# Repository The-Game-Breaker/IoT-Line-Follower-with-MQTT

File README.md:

# IoT Project
# Hardware
## Gebruikte hardware
### Electronica
| Item                            | Discription                                      | Price    | Qty | Extra costs | Total     |
| ------------------------------- | ------------------------------------------------ | -------- | --- | ----------- | --------- |
| Cytron Maker Line               | Simplifying Line Sensor for BeginnersSKU: 19064  |  11,95 € | 1   |             |  11,95 €  |
| Shipping Sensor                 | Shipping elektor                                 |          | 1   |  7,95 €     |  7,95 €   |
| PCB mainboard                   | PCB robot driver board                           |  0,51 €  | 1   |             |  0,51 €   |
| SHIPPING CHARGE                 | SHIPPING                                         |          | 1   |  12,63 €    |  12,63 €  |
| PAYPAL FEE                      | PAYPAL FEE                                       |          | 1   |  0,41 €     |  0,41 €   |
| DRV8825 driver                  | DSD00010 \_Stepstick DRV8825 drive with heatsink |  5,00 €  | 2   |             |  10,00 €  |
| Inbusstelschroef M4x5           | DBM00194 \_Inbusstelschroef M4x5 (10 stuks)      |  2,30 €  | 1   |             |  2,30 €   |
| Verzend- en administratiekosten | Verzend- en administratiekosten 123-3D.nl        |          | 1   |  5,95 €     |  5,95 €   |
| Lipo Battery                    | Yuki Kryptonium 3S 11.1V 30C 5000mAh LiPo 801323 |  45,99 € | 1   |             |  45,99 €  |
| Step-Down Buck Converter        | DEBO DCDC DOWN 4 (mini 360)                      |  2,02 €  | 1   |             |  2,02 €   |
| Dupont kit                      | Dupont connector kit                             |  5,00 €  | 1   |             |  5,00 €   |
| Fuse holder                     | fuse holder                                      |  0,30 €  | 1   |             |  0,30 €   |
| Fuse                            | fuse 2A                                          |  0,20 €  | 1   |             |  0,20 €   |
| RGB led                         | RGB common cathode                               |  1,03 €  | 2   |             |  2,06 €   |
| 3mm led                         | 3mm led red                                      |  0,05 €  | 2   |             |  0,10 €   |
| Resistors                       | resistors various values                         |  0,02 €  | 8   |             |  0,13 €   |
| HC-SR04                         | HC-SR04 Ultrasonic sensor – afstandsmeter        |  3,00 €  | 1   |             |  3,00 €   |
| capacator                       | capacator                                        |  0,11 €  | 2   |             |  0,22 €   |
| 3D print                        | 3d prints materiaal+manafacturing                |  20,00 € | 1   |             |  20,00 €  |
| Lasercut frame                  | laserkcut frame matriaal+manafacturing           |  20,00 € | 1   |             |  20,00 €  |
| Stepper motor                   | JK42HS34-1334                                    |  13,00 € | 2   |             |  26,00 €  |
| Hardware                        | varous nuts and bolts                            |  15,00 € | 1   |             |  15,00 €  |
| Knikkers                        | knikkers                                         |  0,20 €  | 2   |             |  0,40 €   |
|                                 |                                                  |          |     |             |  192,12 € |
#### Cytron Maker-Line

De Cytron Maker-Line is een ir sensor array voorzien van 5 sensoren die de lijn uitlezen. Op basis van deze output sturen we de motoren aan. Deze module geeft ook nog wat extra &quot;creature-comforts&quot;, zo is de array gemakkelijk te kalibreren en kan deze &quot;geswitchted&quot; worden tussen een donkere of lichte lijn.

#### HC-SR04

De HC-SR04 is een ultrasone sensor. Deze moet ervoor zorgen dat het wagentje nergens tegenaan rijdt. Dit wordt tot stand gebracht met ultrasone echolocatie.

#### Joy-IT Esp32

Het brein van het project wordt de ESP32 van JOY-IT. Deze zal alle in- en outputs aansturen en data communiceren via wifi.

### nema17 stepper motor

Deze JK42HS34-1334 NEMA 17 stepper motoren worden gebruikt om het wagentje aan te drijven. Hoewel niet de ideale keuze, bieden ze toch enige flexibiliteit ten opzichte van andere oplossingen. Een andere factor voor deze keuze was dat ik deze nog had liggen en ik er graag eens mee wilde werken.

#### DRV8825 stepper motor driver

De DRV8825 wordt gebruikt om de NEMA 17 motoren aan te sturen. Niet alleen biedt deze driver een hogere ampère levering, de microsteps kunnen ook makkelijk worden ingesteld

#### RGB LED 5mm

Deze led wordt gebruikt als indicator voor de status van het wagentje.

Deze statussen zijn:

- Rood: Het wagentje is de lijn kwijt
- Groen: Het wagentje volgt de lijn en geeft aan naar welke kant er wordt gedraaid
- Blauw: Het wagentje stopt voor een obstakel. Dit kan een blokkade of een dwarslijn zijn.

### Schema, PCB
####

Het onderstaand schema geeft de beschreven componenten systematisch weer.

### Hardware, andere componenten
#### Chassis

Het chassis bestaat uit een eigen ontwerp vervaardigd uit plexiglas en 3D-geprinte (r)PETG-onderdelen. Deze zijn aan elkaar verbonden met M3, M4 en M5 bouten en moeren uit RVS.
#### Wielen

Er zijn 2 wielen voorzien die instaan voor de aandrijving en sturing van het wagentje. Deze komen oorspronkelijk van een RC-auto. Ook zijn er 2 kogelwieltjes voorzien om het wagentje stabiel te houden.
# Code
## Overview
Programmatie werd geschreven in Visual Studio Code met platformio. Dit geeft een aantal voordelen qua debuggen en foutcontrole maar brengt ook een aantal challenges met zich mee. De code wordt opgedeeld in verschillende onderdelen.

### Setup: includes, definities, integers, etc.

Eerst vinden we een sectie met declaraties en setup voor de verschillende onderdelen van het wagentje. Ook vinden we enkele &quot;macro&#39;s&quot;; deze worden gebruikt om de code en functies later leesbaarder te houden.

### Functies
Vervolgens vinden we een sectie waarin de functies zijn geschreven. Deze worden later opgevraagd door de verschillende taken of andere functies.

### Taken

Onder de functies vinden we een sectie met &quot;Tasks&quot;. Hier worden de functies gedeclareerd die later door de ESP&#39;s FreeRTOS zullen worden opgevraagd.

### Setup en Loop

Tot slot vinden we de sectie setup, hier worden de pinnen gedeclareerd en geïnitialiseerd, ook de taken worden hier toegevoegd. De loop-functie wordt in praktijk niet gebruikt in dit geval.

## FreeRTOS

In de programmatie ben ik voor een systeem gegaan met FreeRTOS in plaats van een meer traditioneel systeem. Ik heb hiervoor gekozen omdat dit het gemakkelijk en efficiënt maakt om te multitasken. Het zorgt er ook voor dat in de toekomst uitbreidingen makkelijk mogelijk zijn.

FreeRTOS werkt een beetje als een scheduler, enkel is deze ingebouwd in de ESP en vraagt dus geen extra libraries. Tevens biedt de RTOS ook een uitgebreid pakket aan opties. Zo kan je bijvoorbeeld een bepaalde taak aan een bepaalde &quot;core&quot; toewijzen en zo &quot;echte&quot; synchrone taken uitvoeren.

## Case system

| Case nr. | Sensors | L | ML | M | MR | R | Dist |
| --- | --- | --- | --- | --- | --- | --- | --- |
| 1 | ExtremeLeft | ON | OFF | OFF | OFF | OFF | OFF |
| 2 | HardLeft | ON | ON | OFF | OFF | OFF | OFF |
| 3 | MediumLeft | OFF | ON | OFF | OFF | OFF | OFF |
| 4 | SoftLeft | OFF | ON | ON | OFF | OFF | OFF |
| 5 | Strait | OFF | OFF | ON | OFF | OFF | OFF |
| 6 | SoftRight | OFF | OFF | ON | ON | OFF | OFF |
| 7 | MediumRight | OFF | OFF | OFF | ON | OFF | OFF |
| 8 | HardRight | OFF | OFF | OFF | ON | ON | OFF |
| 9 | ExtremeRight | OFF | OFF | OFF | OFF | ON | OFF |
| 10 | CrossLine | ON | ON | ON | ON | ON | OFF |
| 11 | LOSTLine | OFF | OFF | OFF | OFF | OFF | OFF |
| 12 | Objectdetect | OFF | OFF | OFF | OFF | OFF | ON |

In de programmatie test de microcontroller de sensorwaarde voor verschillende cases. Aan de hand van deze waarde wordt er een &quot;casenummer&quot; gegeven. Deze kan dan worden opgevraagd door een andere taak, in dit geval de motor sturing taak (taskstep).
![](RackMultipart20210601-4-1wbuym5_html_b8db10d83fbda782.png
## Wifi en MQTT

De ESP is voorzien van een &quot;library&quot; waarmee hij via wifi met een mqtt server kan verbinden. Deze kan zowel &quot;subscriben&quot; als &quot;publishen&quot;. Zo kan hij communiceren met de node red server.

# Tutorial

## Prerequisites

Tijdens de tutorial wordt ervan uitgegaan dat er kennis is van volgende elementen:

- Elektronica
- Mechanica
- ESP32 en software
- MQTT
- Node Red
- Netwerken

## Stap 1: Acquiring hardware

De eerste stap om het wagentje te bouwen is natuurlijk alle hardware en elektronica aan te kopen. Deze onderdelen werden eerder in dit document beschreven onder het deel hardware en zijn ook terug te vinden in de BOM.

## Stap 2: Assemblage

Nadat alle onderdelen zijn aangekomen, kunnen we beginnen met de assemblage van de wagentjes.

### Bodem frame

Bevestig de motor houders, zwenkwieltjes en batterijhouder aan het bodem frame met de bijhorende bouten, moeren en rondellen.

### Midden frame

Bevestig de stapper motoren in de motorhouders. Installeer de &quot;support poles&quot; op de bodemplaat. Installeer ook de bumper met line sensor.

### Boven frame

Installeer het boven frame op de &quot;support poles&quot; en bevestig deze. Installeer vervolgens de mounting bracket voor de afstandssenor.

### PCB

Soldeer alle componenten op de PCB behalve de motorkabels.

### Elektronica bevestigen

Bevestig de servo op het mounting bracket. Neem de afstand sensor en installeer deze op het bovendeel van het mounting bracket en installeer het geheel vervolgens op de servomotor. Bevestig vervolgens de pcb met de bijhorende bouten, moeren en &quot;standoffs&quot; op het boven frame.

### Afmontage Elektronica

Tot slot worden alle kabels getrokken en verbonden met de bijhorende onderdelen volgens onderstaand schema.

## Stap 3: MQTT and node red

Installeer een MQTT en Node Red server. Hierbij kan gebruik gemaakt worden van een raspberry pi.

Installeer de node-red flow voor de wagensturing.

## Stap 4: Programmatie ESP32

Nu we een MQTT-server hebben, moeten we de ESP32 programmeren. Vergeet niet voor het programmeren de code aan te passen aan de huidige situatie (wifi ssid, password, etc.). Programmeer vervolgens ESP.

## Stap 5 Aanleggen van het parcours

Het aanleggen van het parcours kan simpelweg worden gedaan door het trekken van een zwarte lijn op lichte grond of witte lijn op donkere grond. Vervolgens kunnen er dwarslijnen voorzien worden om het wagentje te stoppen op de &quot;points of intrest&quot;.

## Stap 6 Tewerkstelling

Tot slot kunnen de wagentjes in werking worden gesteld. Door deze op de lijn te plaatsen en de batterij in te steken.

# Resources

[https://grabcad.com/library/esp-wroom-32-2](https://grabcad.com/library/esp-wroom-32-2)

[https://www.cytron.io/p-maker-line-simplifying-line-sensor-for-beginner](https://www.cytron.io/p-maker-line-simplifying-line-sensor-for-beginner)

[https://www.jkongmotor.com/product/42HS-NEMA17-2Phase-Stepper-Motor-1-8%C2%B0.html](https://www.jkongmotor.com/product/42HS-NEMA17-2Phase-Stepper-Motor-1-8%C2%B0.html)

[https://www.thingiverse.com/thing:4275668/files](https://www.thingiverse.com/thing:4275668/files)

[https://www.makerguides.com/wp-content/uploads/2019/02/DRV8825-Arduino-stepper-motor-wiring-schematic-diagram-pinout\_bb-1024x551.jpg](https://www.makerguides.com/wp-content/uploads/2019/02/DRV8825-Arduino-stepper-motor-wiring-schematic-diagram-pinout_bb-1024x551.jpg)

[https://www.makerguides.com/drv8825-stepper-motor-driver-arduino-tutorial/](https://www.makerguides.com/drv8825-stepper-motor-driver-arduino-tutorial/)

[https://github.com/suzakulab/Eagle-Library-Pololu](https://github.com/suzakulab/Eagle-Library-Pololu)

[https://www.diymodules.org/eagle-show-object?type=dm&amp;file=diy-modules.lbr&amp;device=DC-DC-STEP-DOWN-MP2307](https://www.diymodules.org/eagle-show-object?type=dm&amp;file=diy-modules.lbr&amp;device=DC-DC-STEP-DOWN-MP2307)

[https://www.airspayce.com/mikem/arduino/AccelStepper/index.html](https://www.airspayce.com/mikem/arduino/AccelStepper/index.html)

[https://www.microchip.com/wwwproducts/en/MCP23016](https://www.microchip.com/wwwproducts/en/MCP23016)

[https://www.instructables.com/IO-Expander-for-ESP32-ESP8266-and-Arduino/](https://www.instructables.com/IO-Expander-for-ESP32-ESP8266-and-Arduino/)

[https://github.com/arkhipenko/TaskScheduler](https://github.com/arkhipenko/TaskScheduler)

[https://ozh.github.io/ascii-tables/](https://ozh.github.io/ascii-tables/)

[https://www.studiopieters.nl/esp32-pinout/](https://www.studiopieters.nl/esp32-pinout/)

[https://flows.nodered.org/node/node-red-dashboard](https://flows.nodered.org/node/node-red-dashboard)

## Colors:

 #004146 RGB (0,65,70)
 
 #018076 RGB (1,128,118)
 
 #03BFB5 RGB (3,191,181)
 
 #949398 RGB (148,147,152)
 
 #EFF5F9 RGB (239,245,249)

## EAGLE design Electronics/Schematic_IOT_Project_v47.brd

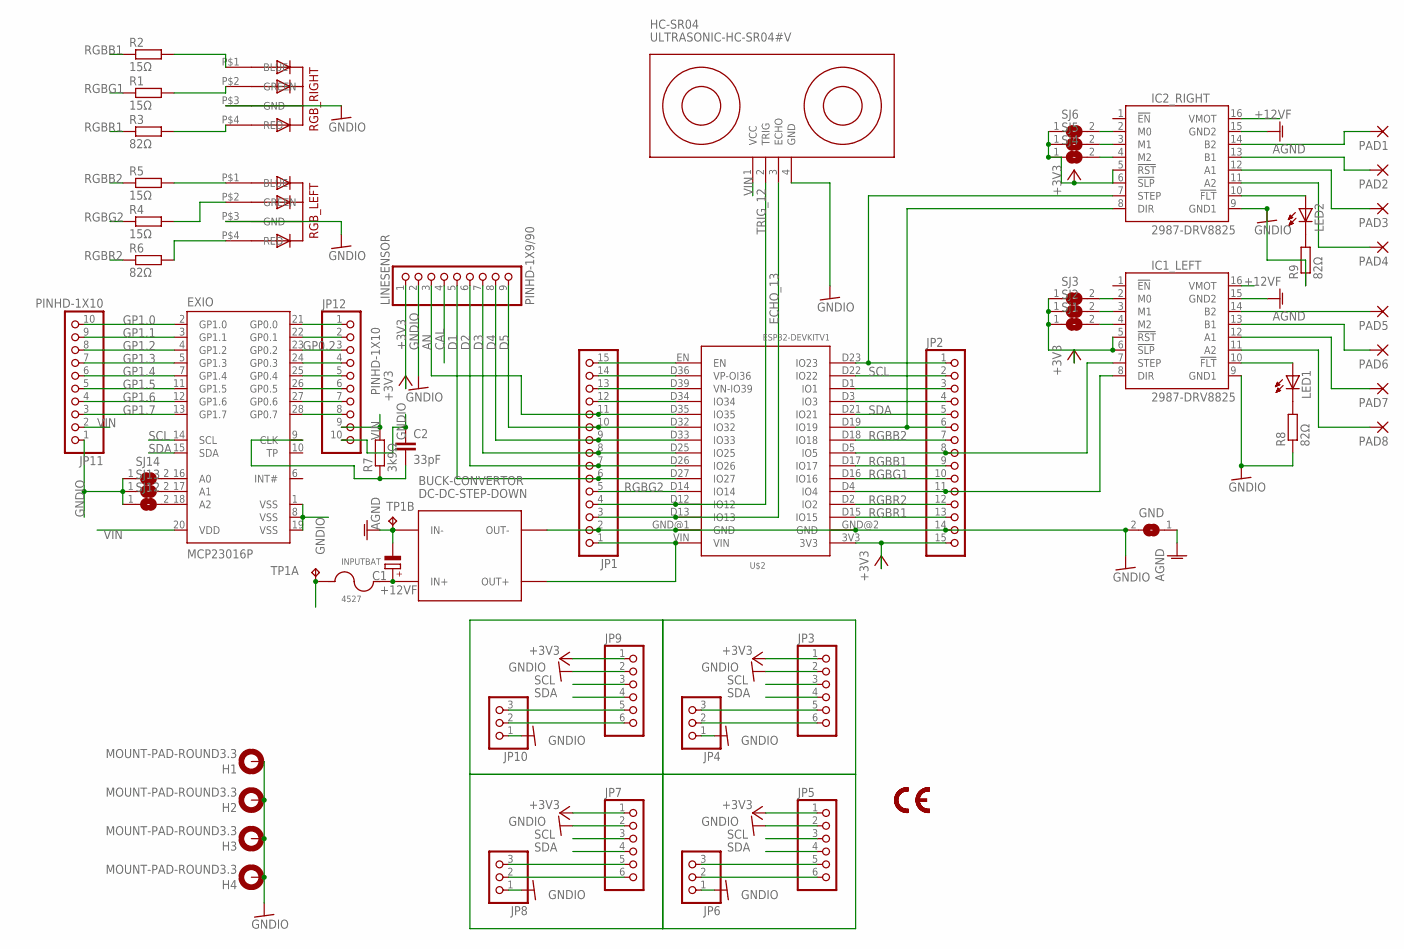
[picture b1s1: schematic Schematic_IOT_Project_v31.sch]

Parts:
BUCK-CONVERTOR: DC-DC-STEP-DOWN; DC-DC-STEP-DOWN-MP2307
C1: CPOL-EUE2,5-6E; E2,5-6E
C2: 33pF; C025-024X044
EXIO: MCP23016P; DIL28-3
GND: SJ
H1, H2, H3, H4: MOUNT-PAD-ROUND3.3; 3,3-PAD
HC-SR04: ULTRASONIC-HC-SR04#V
IC1_LEFT, IC2_RIGHT: 2987-DRV8825; DRV8825
INPUTBAT: 4527
JP1, JP2: PINHD-1X15; 1X15
JP3, JP5, JP7, JP9: PINHD-1X6; 1X06
JP4, JP6, JP8, JP10: PINHD-1X3; 1X03
JP11, JP12: PINHD-1X10; 1X10
LED1, LED2: LED3MM
LINESENSOR: PINHD-1X9/90; 1X09/90
PAD1, PAD2, PAD3, PAD4, PAD5, PAD6, PAD7, PAD8: 1,6/0,8
R1, R2, R4, R5: 15Ω; 0204/7
R3, R6, R8, R9: 82Ω; 0204/7
R7: 3k9Ω; 0204/7
RGB_LEFT: 5MMRGBLED; LED5MMRGB
RGB_RIGHT: 5MMRGBLED; LED5MMRGB
SJ1, SJ2, SJ3, SJ4, SJ5, SJ6, SJ12, SJ13, SJ14: SJ
TP1: TP2P2-38-17; P2-38-17
U$2: ESP32DEVKITV1; ESP32-DEVKITV1

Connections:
+3V3: IC1_LEFT.5 (!RST), IC1_LEFT.6 (!SLP), IC2_RIGHT.5 (!RST), IC2_RIGHT.6 (!SLP), JP2.15, JP3.1, JP5.1, JP7.1, JP9.1, LINESENSOR.1, SJ1.1, SJ2.1, SJ3.1, SJ4.1, SJ5.1, SJ6.1, U$2.3V3
+12VF: BUCK-CONVERTOR.IN+, C1.+, IC1_LEFT.16 (VMOT), IC2_RIGHT.16 (VMOT), INPUTBAT.2
AGND: BUCK-CONVERTOR.IN-, C1.-, GND.1, IC1_LEFT.15 (GND2), IC2_RIGHT.15 (GND2), TP1.TP-2
AN: JP1.11, LINESENSOR.3, U$2.D35 (IO35)
CAL: LINESENSOR.4
D1: JP1.6, LINESENSOR.5, U$2.D27 (IO27)
D2: JP1.7, LINESENSOR.6, U$2.D26 (IO26)
D3: JP1.8, LINESENSOR.7, U$2.D25 (IO25)
D4: JP1.9, LINESENSOR.8, U$2.D33 (IO33)
D5: JP1.10, LINESENSOR.9, U$2.D32 (IO32)
ECHO_13: HC-SR04.3 (ECHO), JP1.3, U$2.D13 (IO13)
GNDIO: BUCK-CONVERTOR.OUT-, C2.1, EXIO.1 (VSS), EXIO.8 (VSS), EXIO.19 (VSS), GND.2, H1.B3,3, H2.B3,3, H3.B3,3, H4.B3,3, HC-SR04.4 (GND), IC1_LEFT.9 (GND1), IC2_RIGHT.9 (GND1), JP1.2, JP2.14, JP3.2, JP4.1, JP5.2, JP6.1, JP7.2, JP8.1, JP9.2, JP10.1, JP11.1, JP12.10, LINESENSOR.2, R8.1, R9.1, RGB_LEFT.P$3 (GND), RGB_RIGHT.P$3 (GND), SJ12.1, SJ13.1, SJ14.1, U$2.GND@1 (GND), U$2.GND@2 (GND)
GP0.0: EXIO.21 (GP0.0), JP12.1
GP0.1: EXIO.22 (GP0.1), JP12.2
GP0.2: EXIO.23 (GP0.2), JP12.3
GP0.3: EXIO.24 (GP0.3), JP12.4
GP0.4: EXIO.25 (GP0.4), JP12.5
GP0.5: EXIO.26 (GP0.5), JP12.6
GP0.6: EXIO.27 (GP0.6), JP12.7
GP0.7: EXIO.28 (GP0.7), JP12.8
GP1.0: EXIO.2 (GP1.0), JP11.10
GP1.1: EXIO.3 (GP1.1), JP11.9
GP1.2: EXIO.4 (GP1.2), JP11.8
GP1.3: EXIO.5 (GP1.3), JP11.7
GP1.4: EXIO.7 (GP1.4), JP11.6
GP1.5: EXIO.11 (GP1.5), JP11.5
GP1.6: EXIO.12 (GP1.6), JP11.4
GP1.7: EXIO.13 (GP1.7), JP11.3
IO23: IC2_RIGHT.7 (STEP), JP2.1, U$2.D23 (IO23)
unnamed: R3.2, RGB_RIGHT.P$4 (RED)
unnamed: R1.2, RGB_RIGHT.P$2 (GREEN)
unnamed: IC1_LEFT.7 (STEP), JP2.8, U$2.D5 (IO5)
unnamed: IC2_RIGHT.8 (DIR), JP2.6, U$2.D19 (IO19)
unnamed: R2.2, RGB_RIGHT.P$1 (BLUE)
unnamed: IC1_LEFT.8 (DIR), JP2.11, U$2.D4 (IO4)
unnamed: R4.2, RGB_LEFT.P$2 (GREEN)
unnamed: IC1_LEFT.4 (M2), SJ1.2
unnamed: IC1_LEFT.3 (M1), SJ2.2
unnamed: IC1_LEFT.2 (M0), SJ3.2
unnamed: R5.2, RGB_LEFT.P$1 (BLUE)
unnamed: R6.2, RGB_LEFT.P$4 (RED)
unnamed: IC2_RIGHT.4 (M2), SJ4.2
unnamed: IC2_RIGHT.3 (M1), SJ5.2
unnamed: IC2_RIGHT.2 (M0), SJ6.2
unnamed: IC2_RIGHT.14 (B2), PAD1.1
unnamed: IC2_RIGHT.13 (B1), PAD2.1
unnamed: IC2_RIGHT.12 (A1), PAD3.1
unnamed: IC2_RIGHT.11 (A2), PAD4.1
unnamed: IC1_LEFT.14 (B2), PAD5.1
unnamed: IC1_LEFT.13 (B1), PAD6.1
unnamed: IC1_LEFT.12 (A1), PAD7.1
unnamed: IC1_LEFT.11 (A2), PAD8.1
unnamed: LED1.K (C), R8.2
unnamed: IC1_LEFT.10 (!FLT), LED1.A
unnamed: LED2.K (C), R9.2
unnamed: JP2.3, U$2.D1 (IO1)
unnamed: JP2.4, U$2.D3 (IO3)
unnamed: IC2_RIGHT.10 (!FLT), LED2.A
unnamed: JP1.15, U$2.EN
unnamed: JP1.14, U$2.D36 (VP-OI36)
unnamed: JP1.13, U$2.D39 (VN-IO39)
unnamed: JP1.12, U$2.D34 (IO34)
unnamed: JP5.5, JP6.3
unnamed: JP5.6, JP6.2
unnamed: JP3.5, JP4.3
unnamed: JP3.6, JP4.2
unnamed: JP7.5, JP8.3
unnamed: JP7.6, JP8.2
unnamed: JP9.5, JP10.3
unnamed: JP9.6, JP10.2
unnamed: C2.2, EXIO.9 (CLK), R7.1
unnamed: INPUTBAT.1, TP1.TP-1
unnamed: EXIO.18 (A2), SJ12.2
unnamed: EXIO.17 (A1), SJ13.2
unnamed: EXIO.16 (A0), SJ14.2
RGBB1: JP2.9, R2.1, U$2.D17 (IO17)
RGBB2: JP2.7, R5.1, U$2.D18 (IO18)
RGBG1: JP2.10, R1.1, U$2.D16 (IO16)
RGBG2: JP1.5, R4.1, U$2.D14 (IO14)
RGBR1: JP2.13, R3.1, U$2.D15 (IO15)
RGBR2: JP2.12, R6.1, U$2.D2 (IO2)
SCL: EXIO.14 (SCL), JP2.2, JP3.3, JP5.3, JP7.3, JP9.3, U$2.D22 (IO22)
SDA: EXIO.15 (SDA), JP2.5, JP3.4, JP5.4, JP7.4, JP9.4, U$2.D21 (IO21)
TRIG_12: HC-SR04.2 (TRIG), JP1.4, U$2.D12 (IO12)
VIN: BUCK-CONVERTOR.OUT+, EXIO.20 (VDD), HC-SR04.1 (VCC), JP1.1, JP11.2, JP12.9, R7.2, U$2.VIN

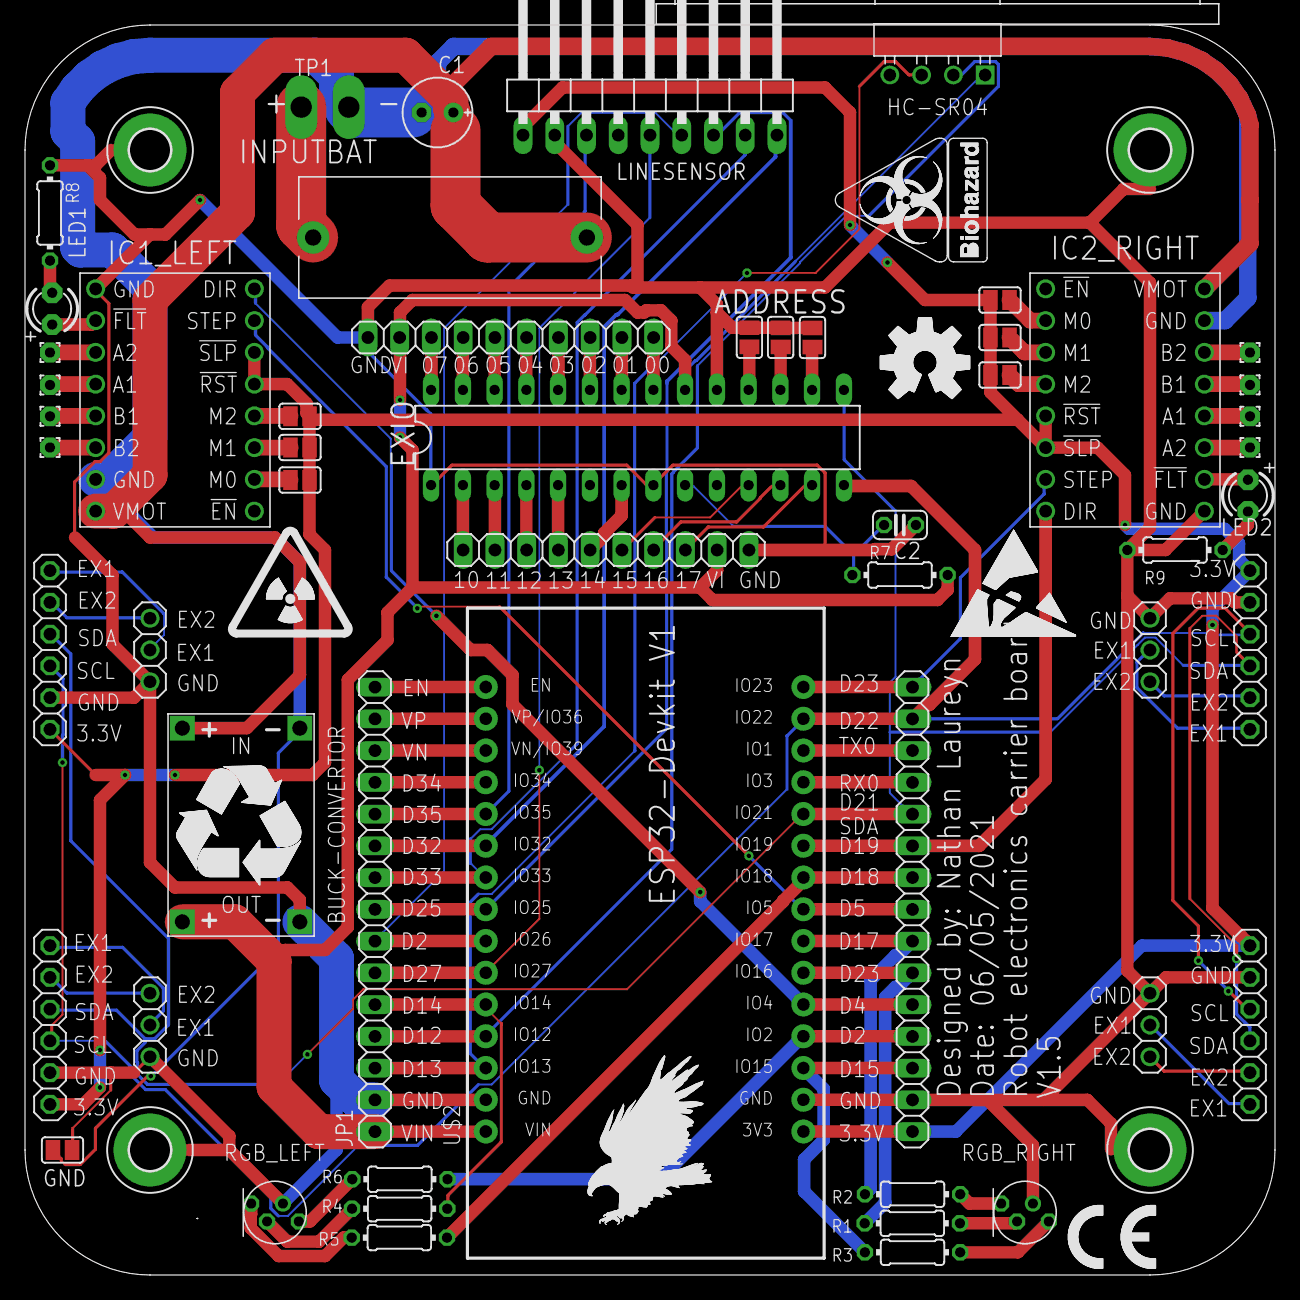
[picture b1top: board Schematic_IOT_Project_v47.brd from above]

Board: 2 copper layers, 100.0 x 100.0 mm, 67 parts (0 on the bottom side), 84 nets.

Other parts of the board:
U$1: LOGO
U$3: CE_5MM
U$4: BIOHAZARD_10.00
U$5: ESD_10.00
U$6: OSHW-LOGO-L
U$7: EAGLE-PLC-10MM
U$8: RADIOACTIVE_10.00
U$9: RECYCLING_10.00
U$10: LOGO02

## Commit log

2021-05-31 Create test
2021-06-01 Added pictures
2021-06-01 Upload of all document files
2021-06-01 Added missing files
2021-06-01 Updated code so it doesn't say "blablabla"
2021-06-02 Added node red flow
2021-06-02 Node red flow

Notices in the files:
parts and their libraries:
diy-modules: Released under the Creative Commons Attribution 4.0 International License: http://creativecommons.org/licenses/by/4.0
SparkFun-Aesthetics: Licensing: Creative Commons ShareAlike 4.0 International - https://creativecommons.org/licenses/by-sa/4.0
